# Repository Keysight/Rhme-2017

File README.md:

# Rhme-2017-2018
Riscure Hack Me embedded hardware CTF 2017-2018

# Pre-qualifications

## Write-ups

* [ResultsMayVary](https://github.com/ResultsMayVary/ctf/tree/master/RHME3)
* [Grazfather](https://grazfather.github.io/ctf/re/crypto/2017/09/03/RHME3-Quals-Whitebox.html)
* [Govanify](https://govanify.com/post/rhme3-quals-ctf/)

# Main Event

## Write-ups
Here's a list of writeups on RHme3. Please add any that are missing

* [S0S1 (2nd place)](https://s0s1-team.github.io/ctf)
* [S0S1 (2nd place)](https://github.com/s0s1-team/ctf/tree/master/rhme3)
* [Cloakware (3rd place)](https://github.com/cloakware-ctf/rhme3-writeups)
* [GabrielGO (5th place)](https://github.com/gabrielgo-ctf/write-ups/tree/master/RHme3)
* [p4 (6th place)](https://github.com/p4-team/ctf/tree/master/2018-04-30-rhme3)
* [TomHaramori (24th place)](https://github.com/haramori/rhme3)
* [Kleinspider (41st place)](https://kleinspider.github.io/writeups/rhme3/overview)

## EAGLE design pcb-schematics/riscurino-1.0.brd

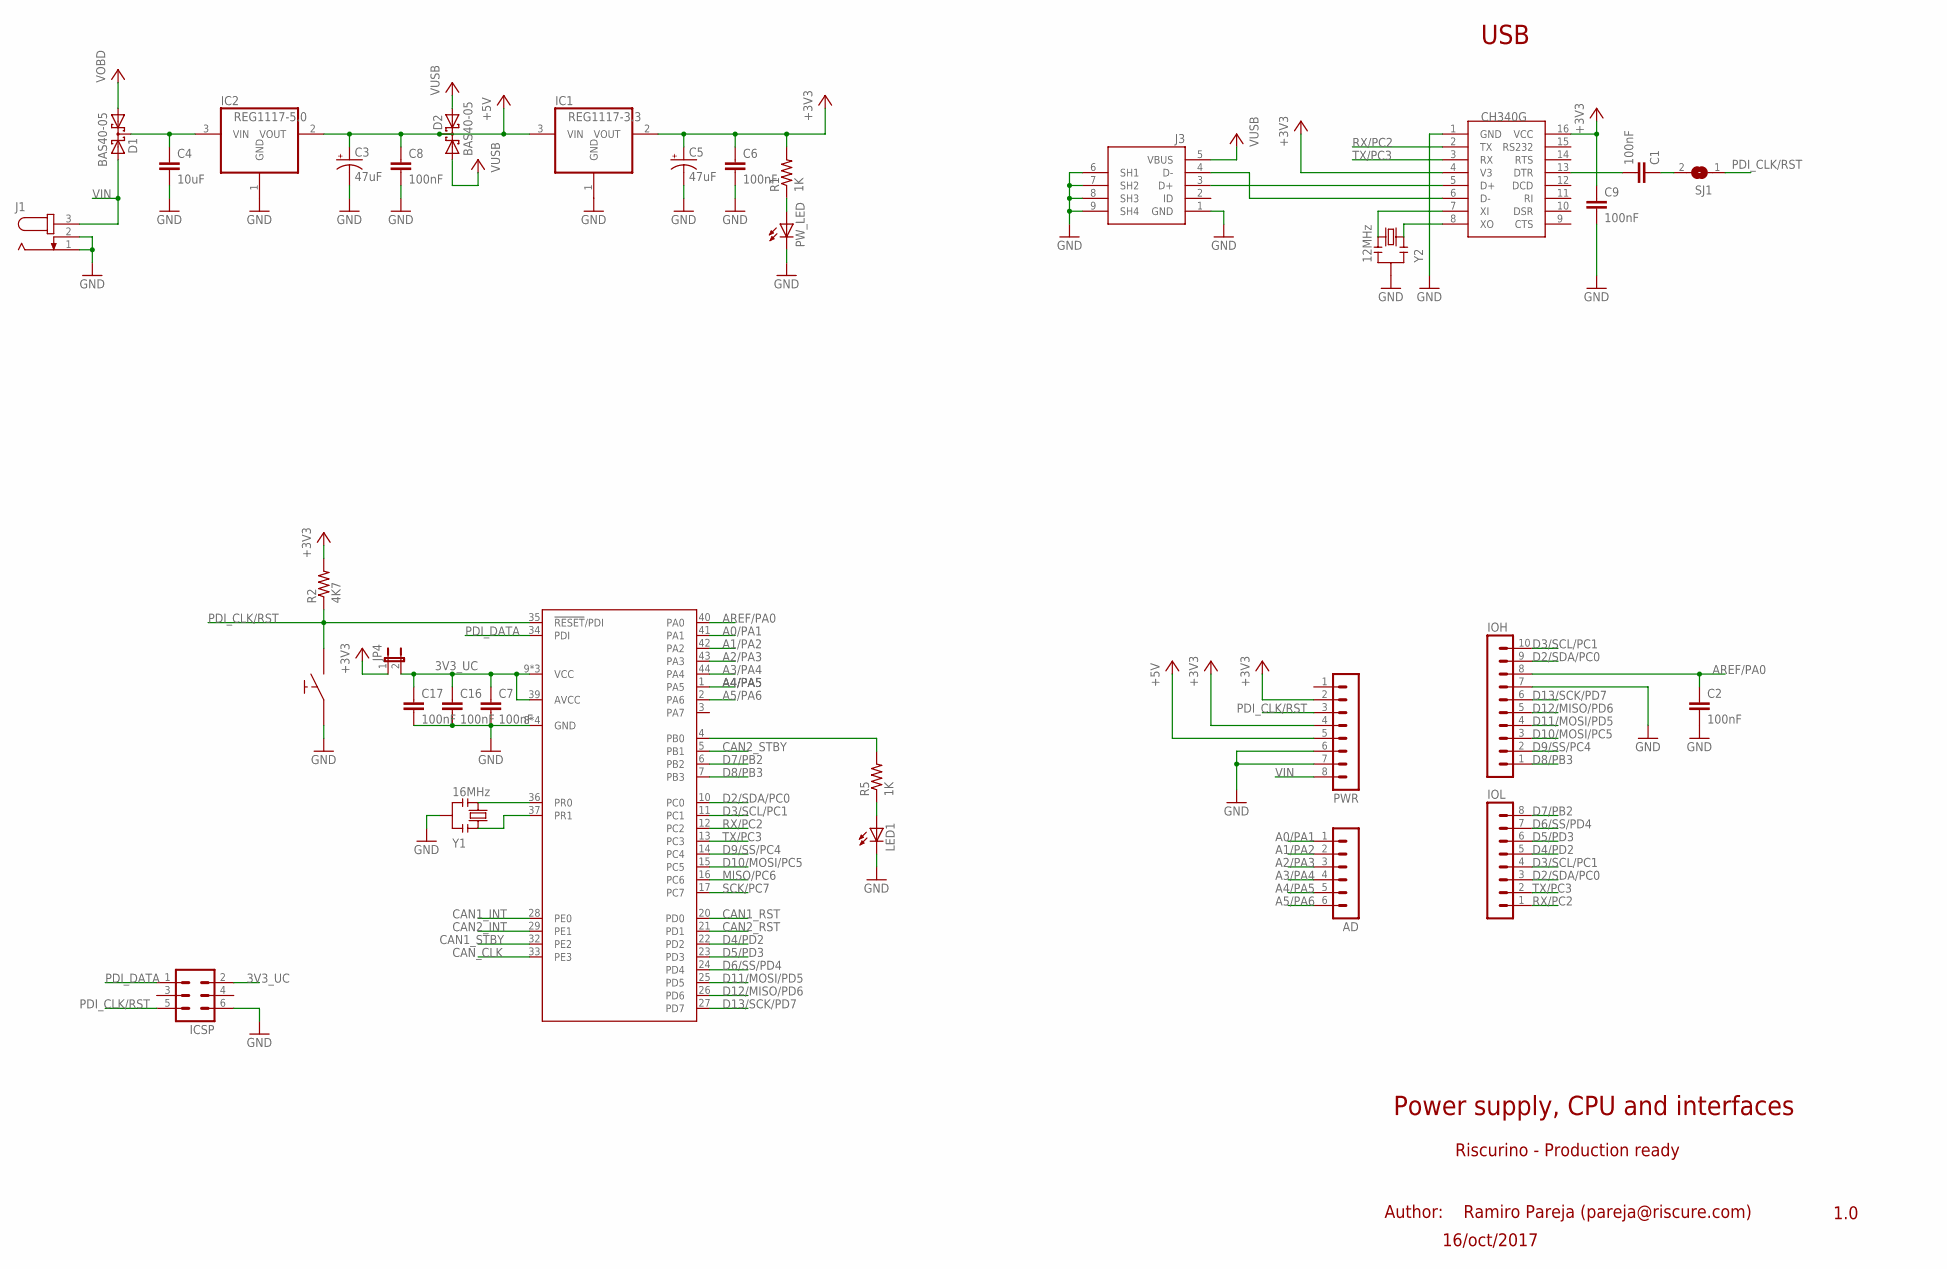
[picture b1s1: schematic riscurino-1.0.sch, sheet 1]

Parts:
AD: MA06-1
C1, C2, C6, C7, C8, C9, C16, C17: 100nF; C0805
C3, C5: 47uF; PANASONIC_C
C4: 10uF; C0805
D1, D2: BAS40-05; SOT23
IC1: REG1117-3.3; SOT223
IC2: REG1117-5.0; SOT223
ICSP: MA03-2
IOH: MA10-1
IOL: MA08-1
J1: JACK-PLUG0; SPC4077
J3: 0219_14850; USB-MINI-B_2
JP4: JP1E; JP1
LED1: LEDCHIPLED_0805; CHIPLED_0805
PWR: MA08-1
PW_LED: LEDCHIPLED_0805; CHIPLED_0805
R1, R5: 1K; R0805
R2: 4K7; R0805
SJ1: SJ
U1: ATXMEGA128A4U-AU; TQFP-44A-44
U4: CH340G; SOIC16
U$1: SWITCH_3X6_BIG
Y1: 16MHz; RESONATOR
Y2: 12MHz; RESONATOR

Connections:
3V3_UC: C7.1, C16.1, C17.1, ICSP.2, JP4.2, U1.9 (VCC), U1.19 (VCC), U1.31 (VCC), U1.39 (AVCC)
+3V3: C5.+, C6.1, C9.1, IC1.2 (VOUT), JP4.1, PWR.2, PWR.4, R1.2, R2.2, U4.4 (V3), U4.16 (VCC); also elsewhere on the board
+5V: C3.+, C8.1, D2.3 (C), IC1.3 (VIN), IC2.2 (VOUT), PWR.5; also elsewhere on the board
A0/PA1: AD.1, U1.41 (PA1)
A1/PA2: AD.2, U1.42 (PA2)
A2/PA3: AD.3, U1.43 (PA3)
A3/PA4: AD.4, U1.44 (PA4)
A4/PA5: AD.5, U1.1 (PA5)
A5/PA6: AD.6, U1.2 (PA6)
AREF/PA0: C2.1, IOH.8, U1.40 (PA0)
CAN1_INT: U1.28 (PE0); also elsewhere on the board
CAN1_RST: U1.20 (PD0); also elsewhere on the board
CAN1_STBY: U1.32 (PE2); also elsewhere on the board
CAN2_INT: U1.29 (PE1); also elsewhere on the board
CAN2_RST: U1.21 (PD1); also elsewhere on the board
CAN2_STBY: U1.5 (PB1); also elsewhere on the board
CAN_CLK: U1.33 (PE3); also elsewhere on the board
D2/SDA/PC0: IOH.9, IOL.3, U1.10 (PC0)
D3/SCL/PC1: IOH.10, IOL.4, U1.11 (PC1)
D4/PD2: IOL.5, U1.22 (PD2)
D5/PD3: IOL.6, U1.23 (PD3)
D6/SS/PD4: IOL.7, U1.24 (PD4); also elsewhere on the board
D7/PB2: IOL.8, U1.6 (PB2)
D8/PB3: IOH.1, U1.7 (PB3)
D9/SS/PC4: IOH.2, U1.14 (PC4); also elsewhere on the board
D10/MOSI/PC5: IOH.3, U1.15 (PC5); also elsewhere on the board
D11/MOSI/PD5: IOH.4, U1.25 (PD5); also elsewhere on the board
D12/MISO/PD6: IOH.5, U1.26 (PD6); also elsewhere on the board
D13/SCK/PD7: IOH.6, U1.27 (PD7); also elsewhere on the board
GND: C2.2, C3.-, C4.2, C5.-, C6.2, C7.2, C8.2, C9.2, C16.2, C17.2, IC1.1 (GND), IC2.1 (GND), ICSP.6, IOH.7, J1.1, J1.2, J3.1 (GND), J3.6 (SH1), J3.7 (SH2), J3.8 (SH3), J3.9 (SH4), LED1.C, PWR.6, PWR.7, PW_LED.C, U1.8 (GND), U1.18 (GND), U1.30 (GND), U1.38 (GND), U4.1 (GND), U$1.P$1, Y1.2, Y2.2; also elsewhere on the board
MISO/PC6: U1.16 (PC6); also elsewhere on the board
unnamed: U1.36 (PR0), Y1.3
unnamed: U1.37 (PR1), Y1.1
unnamed: C1.2, U4.13 (DTR)
unnamed: C4.1, D1.3 (C), IC2.3 (VIN)
unnamed: J3.3 (D+), U4.5 (D+)
unnamed: PW_LED.A, R1.1
unnamed: J3.4 (D-), U4.6 (D-)
unnamed: LED1.A, R5.1
unnamed: C1.1, SJ1.2
unnamed: U4.8 (XO), Y2.1
unnamed: U4.7 (XI), Y2.3
unnamed: R5.2, U1.4 (PB0)
PDI_CLK/RST: ICSP.5, PWR.3, R2.1, SJ1.1, U1.35 (!RESET!/PDI), U$1.P$2
PDI_DATA: ICSP.1, U1.34 (PDI)
RX/PC2: IOL.1, U1.12 (PC2), U4.2 (TX)
SCK/PC7: U1.17 (PC7); also elsewhere on the board
TX/PC3: IOL.2, U1.13 (PC3), U4.3 (RX)
VIN: D1.2 (A2), J1.3, PWR.8
VOBD: D1.1 (A1); also elsewhere on the board
VUSB: D2.1 (A1), D2.2 (A2), J3.5 (VBUS)

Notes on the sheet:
USB
Riscurino - Production ready
1.0
16/oct/2017
Author: Ramiro Pareja (pareja@riscure.com)
Power supply, CPU and interfaces

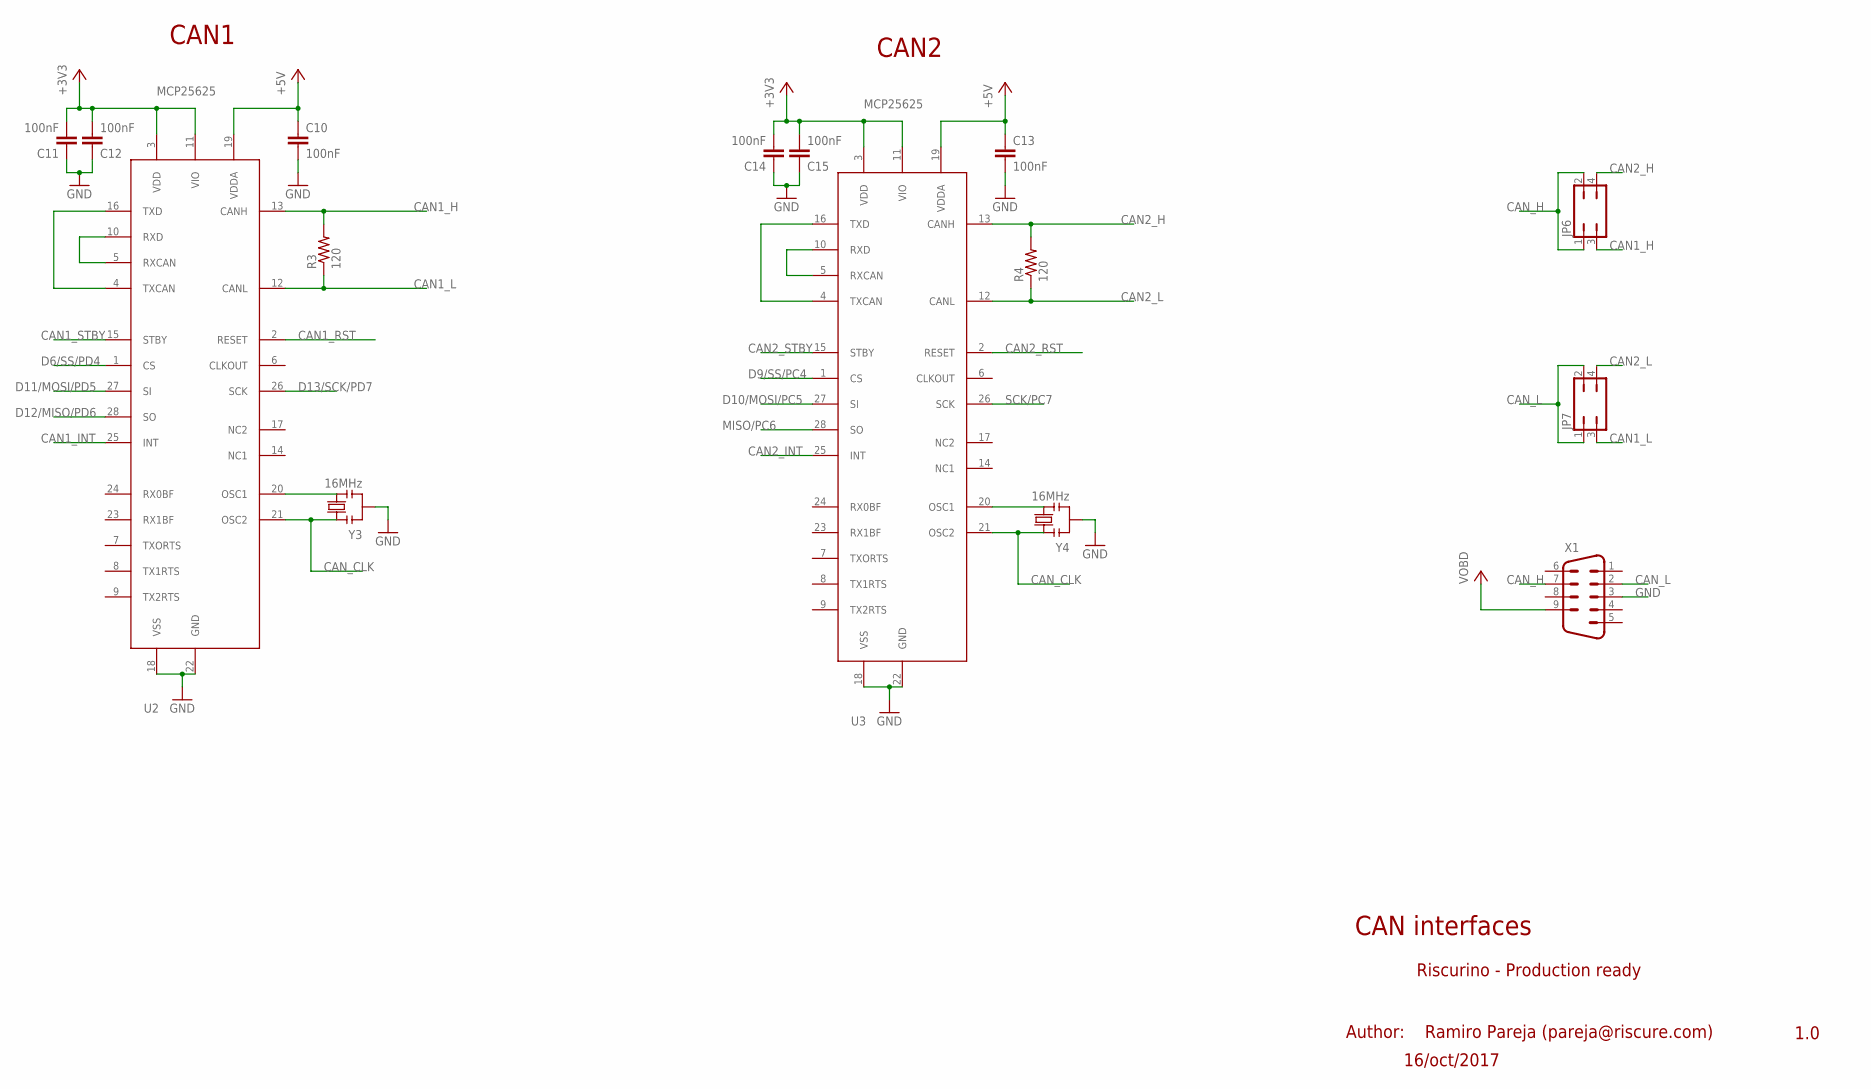
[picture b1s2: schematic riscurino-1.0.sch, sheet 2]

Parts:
C10, C11, C12, C13, C14, C15: 100nF; C0805
JP6, JP7: JP2Q
R3, R4: 120; R0805
U2, U3: MCP25625; QFN28
X1: M09HP
Y3, Y4: 16MHz; RESONATOR

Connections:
+3V3: C11.2, C12.2, C14.2, C15.2, U2.3 (VDD), U2.11 (VIO), U3.3 (VDD), U3.11 (VIO); also elsewhere on the board
+5V: C10.1, C13.1, U2.19 (VDDA), U3.19 (VDDA); also elsewhere on the board
CAN1_H: JP6.3, R3.2, U2.13 (CANH)
CAN1_INT: U2.25 (INT); also elsewhere on the board
CAN1_L: JP7.3, R3.1, U2.12 (CANL)
CAN1_RST: U2.2 (RESET); also elsewhere on the board
CAN1_STBY: U2.15 (STBY); also elsewhere on the board
CAN2_H: JP6.4, R4.2, U3.13 (CANH)
CAN2_INT: U3.25 (INT); also elsewhere on the board
CAN2_L: JP7.4, R4.1, U3.12 (CANL)
CAN2_RST: U3.2 (RESET); also elsewhere on the board
CAN2_STBY: U3.15 (STBY); also elsewhere on the board
CAN_CLK: U2.21 (OSC2), U3.21 (OSC2), Y3.1, Y4.1; also elsewhere on the board
CAN_H: JP6.1, JP6.2, X1.7
CAN_L: JP7.1, JP7.2, X1.2
D6/SS/PD4: U2.1 (CS); also elsewhere on the board
D9/SS/PC4: U3.1 (CS); also elsewhere on the board
D10/MOSI/PC5: U3.27 (SI); also elsewhere on the board
D11/MOSI/PD5: U2.27 (SI); also elsewhere on the board
D12/MISO/PD6: U2.28 (SO); also elsewhere on the board
D13/SCK/PD7: U2.26 (SCK); also elsewhere on the board
GND: C10.2, C11.1, C12.1, C13.2, C14.1, C15.1, U2.18 (VSS), U2.22 (GND), U3.18 (VSS), U3.22 (GND), X1.3, Y3.2, Y4.2; also elsewhere on the board
MISO/PC6: U3.28 (SO); also elsewhere on the board
unnamed: U3.4 (TXCAN), U3.16 (TXD)
unnamed: U2.4 (TXCAN), U2.16 (TXD)
unnamed: U2.5 (RXCAN), U2.10 (RXD)
unnamed: U3.5 (RXCAN), U3.10 (RXD)
unnamed: U2.20 (OSC1), Y3.3
unnamed: U3.20 (OSC1), Y4.3
SCK/PC7: U3.26 (SCK); also elsewhere on the board
VOBD: X1.9; also elsewhere on the board

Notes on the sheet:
CAN1
CAN2
Riscurino - Production ready
1.0
16/oct/2017
Author: Ramiro Pareja (pareja@riscure.com)
CAN interfaces

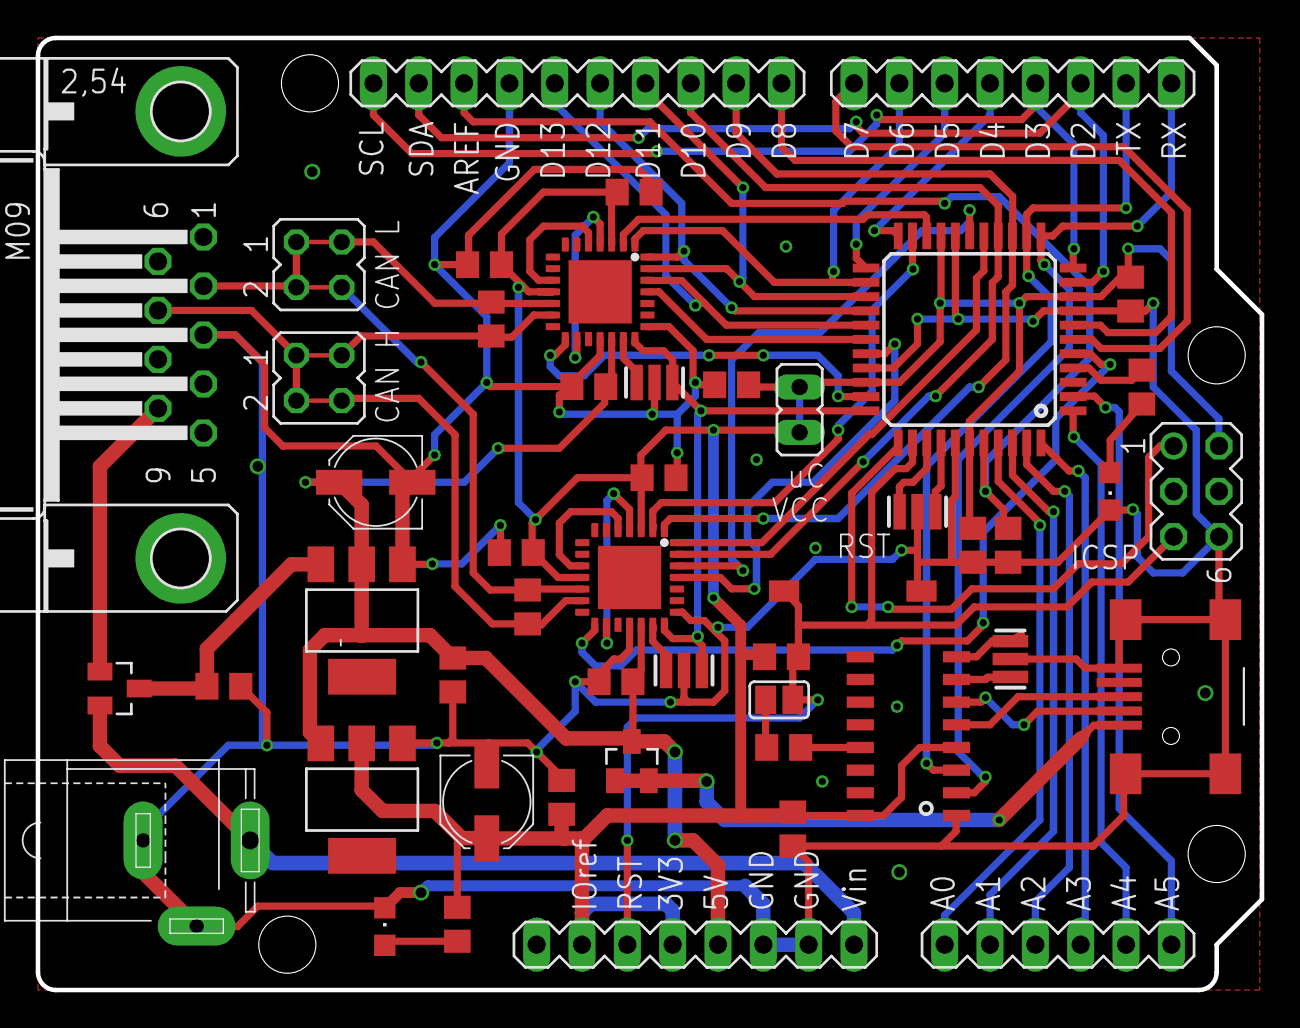
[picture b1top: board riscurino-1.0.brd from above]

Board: 2 copper layers, 68.6 x 53.3 mm, 49 parts (0 on the bottom side), 63 nets.

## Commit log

2017-08-30 RHme3 prequalification challenges
2017-08-30 adding exploitation + changing .gitignore
2018-01-22 added the pcb schematics
2018-02-13 Correct schematics and PCB uploaded.
2018-05-24 Added main event write-ups
2018-05-24 Fixed README.md markup
2018-05-24 Added some prequals write-ups
